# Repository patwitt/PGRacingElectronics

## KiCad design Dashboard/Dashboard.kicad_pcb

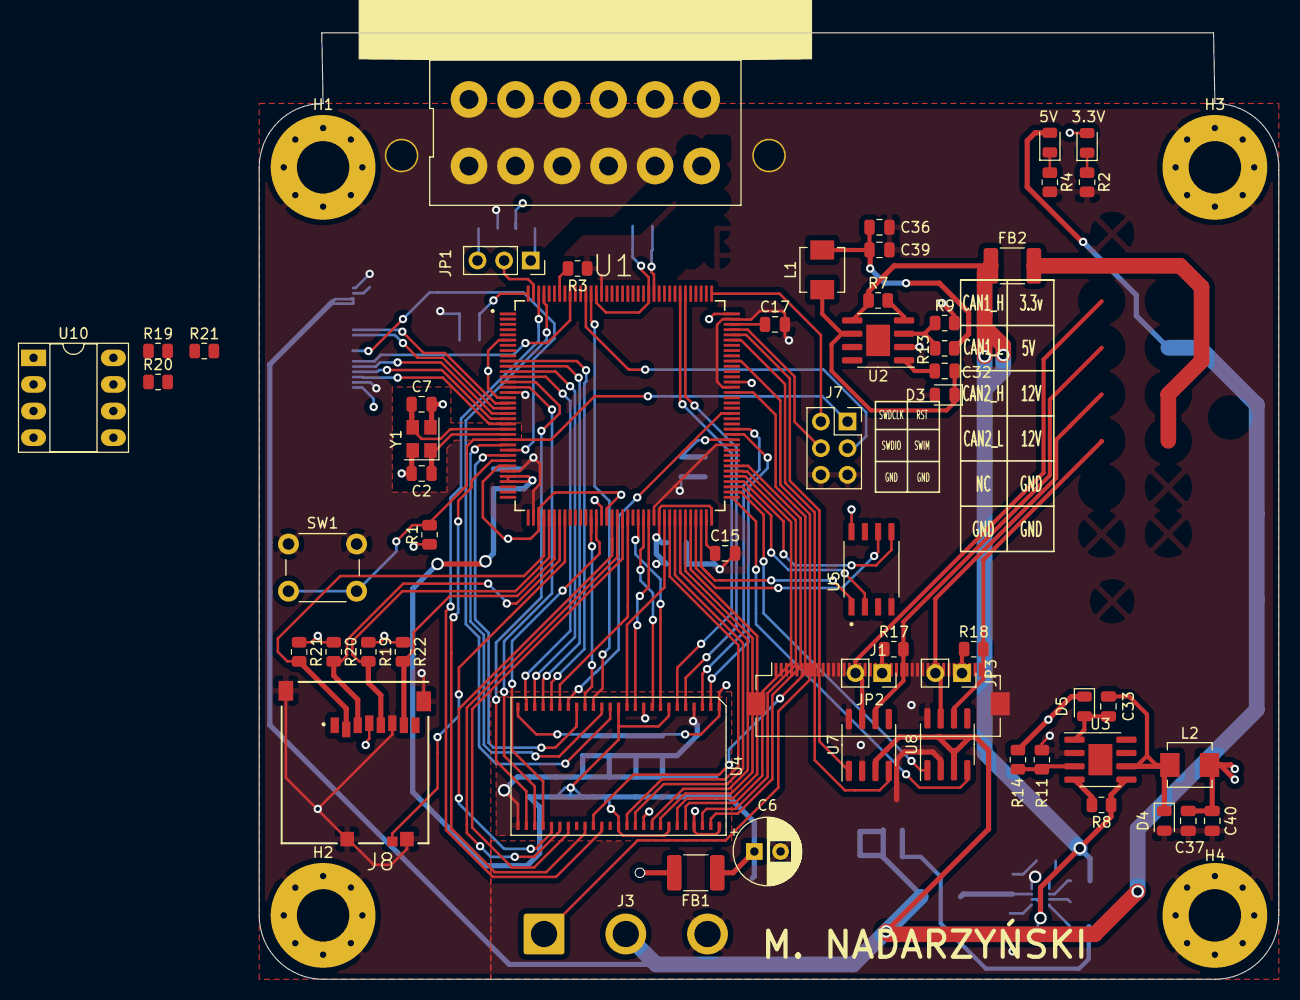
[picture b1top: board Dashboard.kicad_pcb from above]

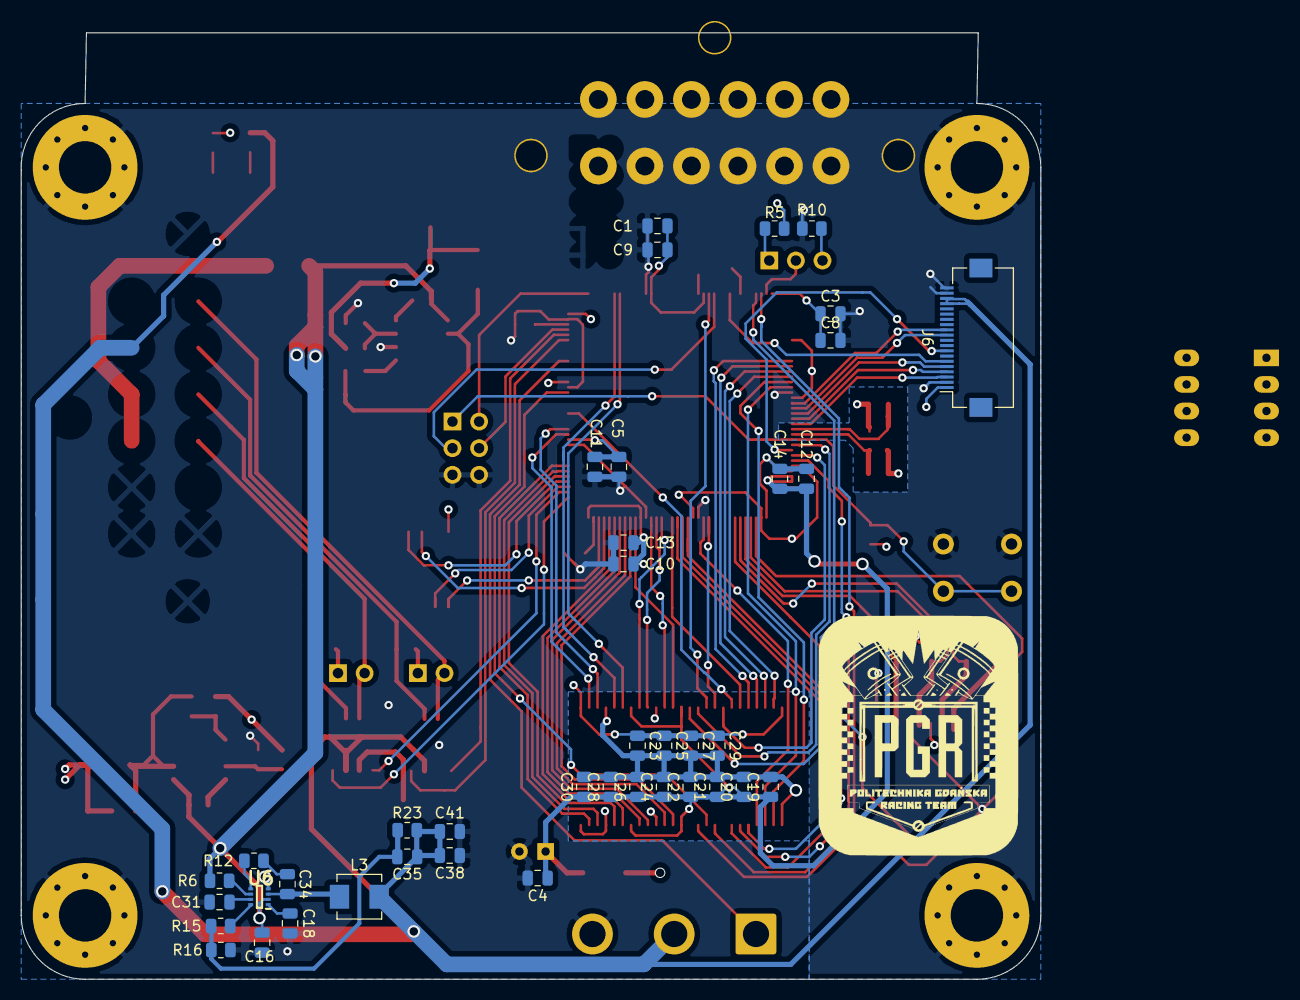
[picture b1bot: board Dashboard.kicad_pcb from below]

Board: 4 copper layers, 97.3 x 90.3 mm, 101 parts (40 on the bottom side), 125 nets.

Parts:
C1, C3, C4, C5, C8, C9, C10, C11, C13, C16, C19, C20, C21, C22, C23, C24, C25, C26, C27, C28, C29, C30: 100nF; C_0805_2012Metric
C2, C7: 14p; C_0805_2012Metric
C6: 470uF; CP_Radial_D6.3mm_P2.50mm
C12, C18, C31, C34: 1uF; C_0805_2012Metric
C14, C32, C33: 10nF; C_0805_2012Metric
C15, C17: 2.2uF; C_0805_2012Metric
C35: 10pF; C_0805_2012Metric
C36, C37, C39, C40: 10uF; C_0805_2012Metric
C38, C41: 22uF; C_0805_2012Metric
D1: LED_3.3V; LED_0805_2012Metric
D2: LED_5V; LED_0805_2012Metric
D3, D4: D_Schottky; D_0805_2012Metric
D5: 1N4148; D_0805_2012Metric
FB1, FB2: Ferrite_Bead; C_1812_4532Metric
H1, H2, H3, H4: MountingHole_Pad; MountingHole_5mm_Pad_Via
J1: Display; Hirose_FH12-40S-0.5SH_1x40-1MP_P0.50mm_Horizontal
J3: LED; SolderWire-2sqmm_1x03_P7.8mm_D2mm_OD3.9mm
J4: MAIN_CONNECTOR; DT13
J6: Display; Hirose_FH12-20S-0.5SH_1x20-1MP_P0.50mm_Horizontal
J7: PROGRAMMER; PinSocket_2x03_P2.54mm_Vertical
J8: MEM2051-00-195-00-A_REVC; GCT_MEM2051-00-195-00-A_REVC
JP1: PDR_ON; PinSocket_1x03_P2.54mm_Vertical
JP2: CAN1_RESISTOR; PinSocket_1x02_P2.54mm_Vertical
JP3: CAN2_RESISTOR; PinSocket_1x02_P2.54mm_Vertical
L1, L2: 10uH; L_Vishay_IHLP-1616
L3: 2.2uH; L_Vishay_IHLP-1616
R1, R3, R5, R10, R19, R20, R21: 10k; R_0805_2012Metric
R2, R4, R9, R11, R12, R13, R14: R; R_0805_2012Metric
R6, R7, R8: 100k; R_0805_2012Metric
R15: 20k; R_0805_2012Metric
R16: 13k; R_0805_2012Metric
R17, R18: 120; R_0805_2012Metric
R19#2, R20#2, R21#2, R22: 47K; R_0805_2012Metric
R23: 40.2k; R_0805_2012Metric
SW1: SW_SPST; SW_PUSH_6mm_H8mm
U1: STM32F767ZIT6; QFP50P2200X2200X160-144N
U2, U3: MP2359DJ-LF-Z; SOIC-8-1EP_3.9x4.9mm_P1.27mm_EP2.29x3mm
U4: AS4C1M16S-6TCN; TSOP-II-50
U5: AT25SF128A-SHB-T; SOIC127P790X216-8N
U6: MP2332H; SOTFL50P160X60-8N
U7, U8: MCP2561-E-SN; SOIC-8_3.9x4.9mm_P1.27mm
U10: 24LC01; DIP-8_W7.62mm_Socket_LongPads
Y1: Crystal_GND24; Crystal_SMD_3225-4Pin_3.2x2.5mm

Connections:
+3.3VA: C4.1, C6.1, C12.1, C14.1, C19.1, C20.1, C21.1, C22.1, C24.1, C26.1, C28.1, C30.1, FB1.1, U1.32, U1.33, U4.7, U4.13, U4.38, U4.44
+3V3: C1.1, C3.1, C5.1, C8.1, C9.1, C10.1, C11.1, C13.1, C23.1, C25.1, C27.1, C29.1, C37.2, C40.2, D1.2, D5.1, FB1.2, J1.4, J4.12, J6.1, J8.4, L2.2, R1.1, R5.1, R14.2, R19#2.1, R20#2.1, R21#2.1, R22.1, U1.6, U1.17, U1.30, U1.39, U1.52, U1.62, U1.72, U1.84, U1.95, U1.108, U1.121, U1.131, U1.144, U4.1, U4.25, U5.8, U10.8
+5V: C35.2, C38.2, C41.2, D2.2, J1.2, J3.2, J4.11, J6.17, J6.18, L3.2, R23.2, U7.3, U8.3
+8V: C36.2, C39.2, L1.2, R13.2
+12L: C16.1, FB2.1, R6.1, R7.1, R8.1, U2.5, U3.5, U6.2
+12V: FB2.2, J4.9, J4.10
/FMC_A0: U1.10, U4.21
/FMC_A1: U1.11, U4.22
/FMC_A2: U1.12, U4.23
/FMC_A3: U1.13, U4.24
/FMC_A4: U1.14, U4.27
/FMC_A5: U1.15, U4.28
/FMC_A6: U1.50, U4.29
/FMC_A7: U1.53, U4.30
/FMC_A8: U1.54, U4.31
/FMC_A9: U1.55, U4.32
/FMC_A10: U1.56, U4.20
/FMC_BA0: U1.89, U4.19
/FMC_D0: U1.85, U4.2
/FMC_D1: U1.86, U4.3
/FMC_D2: U1.114, U4.5
/FMC_D3: U1.115, U4.6
/FMC_D4: U1.58, U4.8
/FMC_D5: U1.59, U4.9
/FMC_D6: U1.60, U4.11
/FMC_D7: U1.63, U4.12
/FMC_D8: U1.64, U4.39
/FMC_D9: U1.65, U4.40
/FMC_D10: U1.66, U4.42
/FMC_D11: U1.67, U4.43
/FMC_D12: U1.68, U4.45
/FMC_D13: U1.77, U4.46
/FMC_D14: U1.78, U4.48
/FMC_D15: U1.79, U4.49
/FMC_NBL0: U1.141, U4.14
/FMC_NBL1: U1.142, U4.36
/FMC_SDCAS: U1.132, U4.16
/FMC_SDCKE0: U1.29, U4.34
/FMC_SDCLK: U1.93, U4.35
/FMC_SDNE0: U1.28, U4.18
/FMC_SDNRAS: U1.49, U4.17
/FMC_SDNWE: U1.43, U4.15
/I2C3_SCL: U1.100, U10.6
/I2C3_SDA: U1.99, U10.5
/LTDC_B0: J1.21, U1.3
/LTDC_B1: J1.22, U1.102
/LTDC_B2: J1.23, U1.122
/LTDC_B3: J1.24, U1.126
/LTDC_B4: J1.25, U1.127
/LTDC_B5: J1.26, U1.37
/LTDC_B6: J1.27, U1.139
/LTDC_B7: J1.28, U1.140
/LTDC_CLK: J1.30, U1.92
/LTDC_DE: J1.34, U1.22
/LTDC_G0: J1.13, U1.4
/LTDC_G1: J1.14, U1.5
/LTDC_G2: J1.15, U1.42
/LTDC_G3: J1.16, U1.125
/LTDC_G4: J1.17, U1.69
/LTDC_G5: J1.18, U1.70
/LTDC_G6: J1.19, U1.97
/LTDC_G7: J1.20, U1.117
/LTDC_HSYNC: J1.32, U1.96
/LTDC_R0: J1.5, U1.128
/LTDC_R1: J1.6, U1.36
/LTDC_R2: J1.7, U1.35
/LTDC_R3: J1.8, U1.46
/LTDC_R4: J1.9, U1.41
/LTDC_R5: J1.10, U1.26
/LTDC_R6: J1.11, U1.47
/LTDC_R7: J1.12, U1.91
/LTDC_VSYNC: J1.33, U1.40
/QUADSPI_IO0: U1.20, U5.5
/QUADSPI_IO1: U1.21, U5.2
/QUADSPI_IO2: U1.19, U5.3
/QUADSPI_IO3: U1.18, U5.7
/QUADSPI_NCS: U1.136, U5.1
/SD_CARD_DETECT: J8.9, U1.44
/SD_CS: J8.2, R21#2.2
/SD_MISO: J8.7, R22.2
/SD_MOSI: J8.3, R20#2.2
/SD_SCLK: J8.5, R19#2.2
CAN_1_1: U1.104, U7.1
CAN_1_2: U1.103, U7.4
CAN_2_1: U1.74, U8.1
CAN_2_2: U1.73, U8.4
CAN_H1: J4.1, JP2.2, U7.7
CAN_H2: J4.3, JP3.2, U8.7
CAN_L1: J4.2, R17.2, U7.6
CAN_L2: J4.4, R18.2, U8.6
GND: C1.2, C2.2, C3.2, C4.2, C5.2, C6.2, C7.2, C8.2, C9.2, C10.2, C11.2, C12.2, C13.2, C14.2, C15.2, C16.2, C17.2, C18.1, C19.2, C20.2, C21.2, C22.2, C23.2, C24.2, C25.2, C26.2, C27.2, C28.2, C29.2, C30.2, C31.1, C36.1, C37.1, C38.1, C39.1, C40.1, C41.1, D3.2, D4.2, H1.1, H2.1, H3.1, H4.1, J1.1, J1.3, J1.29, J1.36, J3.3, J4.6, J4.7, J4.8, J4.14, J4.15, J6.2, J6.19, J6.20, J7.5, J7.6, J8.6, J8.10, J8.11, J8.12, J8.13, R2.2, R3.1, R4.2, R9.2, R10.2, R11.2, R16.2, R21.1, SW1.1, U1.16, U1.31, U1.38, U1.51, U1.61, U1.83, U1.94, U1.107, U1.120, U1.130, U2.2, U3.2, U4.4, U4.10, U4.26, U4.41, U4.47, U4.50, U5.4, U6.4, U7.2, U7.8, U8.2, U8.8, U10.1, U10.2, U10.3, U10.4, Y1.2, Y1.4
LED_DATA: J3.1, U1.134
unnamed: C2.1, U1.24, Y1.1
unnamed: C7.1, U1.23, Y1.3
unnamed: C18.2, U6.1
unnamed: C31.2, U6.7
unnamed: C32.1, U2.1
unnamed: C32.2, D3.1, L1.1, U2.6
unnamed: C33.1, D5.2, U3.1
unnamed: C33.2, D4.1, L2.1, U3.6
unnamed: C34.1, R12.1
unnamed: C34.2, L3.1, U6.3
unnamed: C35.1, R15.1, R16.1, R23.1
unnamed: D1.1, R2.1
unnamed: D2.1, R4.1
unnamed: JP1.1, R5.2
unnamed: JP1.2, U1.143
unnamed: JP1.3, R10.1
unnamed: JP2.1, R17.1
unnamed: JP3.1, R18.1
unnamed: R3.2, U1.138
unnamed: R6.2, U6.6
unnamed: R7.2, U2.4
unnamed: R8.2, U3.4
unnamed: R11.1, R14.1, U3.3
unnamed: R12.2, U6.5
unnamed: R9.1, R13.1, U2.3
unnamed: R15.2, U6.8
unnamed: R21.2, U10.7
RST: J7.1, R1.2, SW1.2, U1.25
SWDCLK: J7.2, U1.109
SWDIO: J7.4, U1.105
SWIM: J7.3, U1.133
VCAP1: C15.1, U1.71
VCAP2: C17.1, U1.106

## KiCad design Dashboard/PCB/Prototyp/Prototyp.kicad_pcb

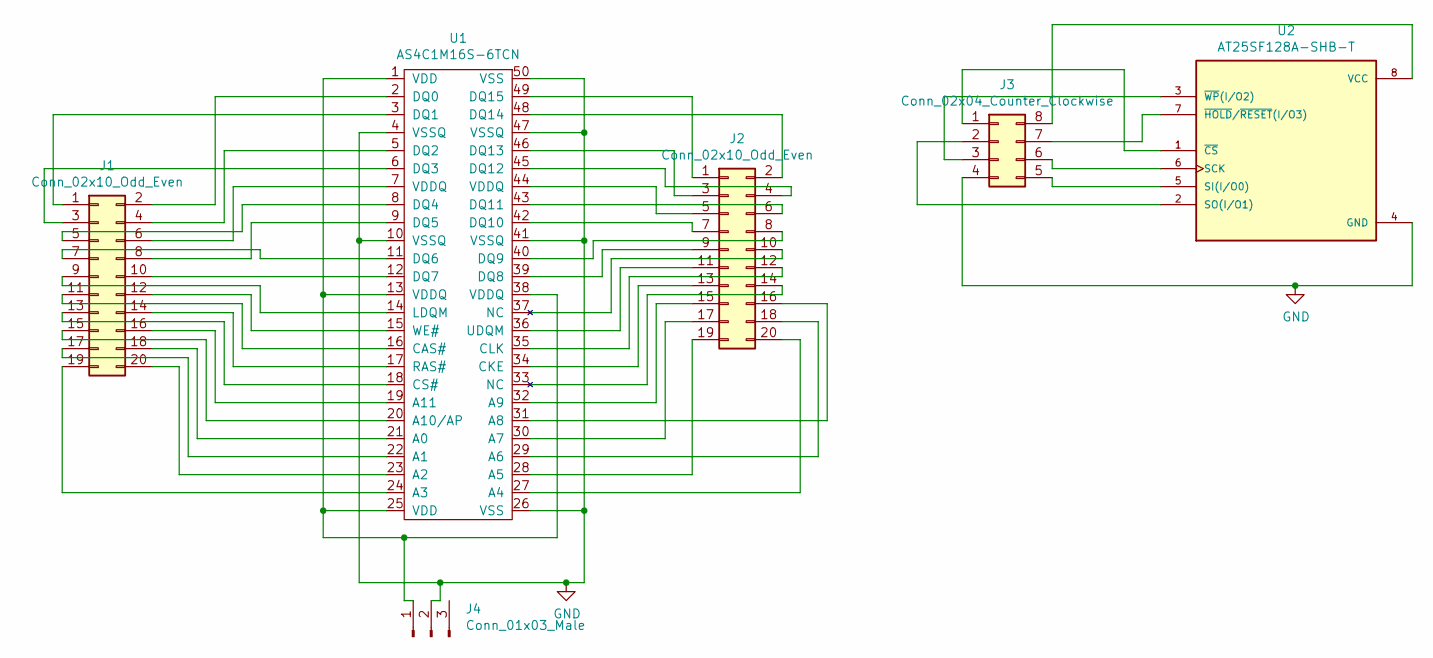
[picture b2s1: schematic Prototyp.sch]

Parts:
J1, J2: Conn_02x10_Odd_Even; PinSocket_2x10_P2.54mm_Vertical
J3: Conn_02x04_Counter_Clockwise; PinSocket_2x04_P2.54mm_Vertical
J4: Conn_01x03_Male; PinSocket_1x03_P2.54mm_Vertical
U1: AS4C1M16S-6TCN; TSOP-II-50
U2: AT25SF128A-SHB-T; SOIC127P790X216-8N; PARTREV F

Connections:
GND: J3.4, J4.2, U1.4 (VSSQ), U1.10 (VSSQ), U1.26 (VSS), U1.41 (VSSQ), U1.47 (VSSQ), U1.50 (VSS), U2.4 (GND)
unnamed: J1.1, U1.3 (DQ1)
unnamed: J1.2, U1.2 (DQ0)
unnamed: J1.3, U1.6 (DQ3)
unnamed: J1.4, U1.5 (DQ2)
unnamed: J1.5, U1.8 (DQ4)
unnamed: J1.6, U1.7 (VDDQ)
unnamed: J1.7, U1.11 (DQ6)
unnamed: J1.8, U1.9 (DQ5)
unnamed: J1.9, U1.14 (LDQM)
unnamed: J1.10, U1.12 (DQ7)
unnamed: J1.11, U1.16 (CAS#)
unnamed: J1.12, U1.15 (WE#)
unnamed: J1.13, U1.18 (CS#)
unnamed: J1.14, U1.17 (RAS#)
unnamed: J1.15, U1.20 (A10/AP)
unnamed: J1.16, U1.19 (A11)
unnamed: J1.17, U1.22 (A1)
unnamed: J1.18, U1.21 (A0)
unnamed: J1.19, U1.24 (A3)
unnamed: J1.20, U1.23 (A2)
unnamed: J2.1, U1.49 (DQ15)
unnamed: J2.2, U1.48 (DQ14)
unnamed: J2.3, U1.46 (DQ13)
unnamed: J2.4, U1.45 (DQ12)
unnamed: J2.5, U1.44 (VDDQ)
unnamed: J2.6, U1.43 (DQ11)
unnamed: J2.7, U1.42 (DQ10)
unnamed: J2.8, U1.40 (DQ9)
unnamed: J2.9, U1.39 (DQ8)
unnamed: J2.10, U1.37 (NC)
unnamed: J2.11, U1.36 (UDQM)
unnamed: J2.12, U1.35 (CLK)
unnamed: J2.13, U1.34 (CKE)
unnamed: J2.14, U1.33 (NC)
unnamed: J2.15, U1.32 (A9)
unnamed: J2.16, U1.31 (A8)
unnamed: J2.17, U1.30 (A7)
unnamed: J2.18, U1.29 (A6)
unnamed: J2.19, U1.28 (A5)
unnamed: J2.20, U1.27 (A4)
unnamed: J3.1, U2.1 (~CS)
unnamed: J3.2, U2.2 (SO(I/O1))
unnamed: J3.3, U2.3 (~WP~(I/O2))
unnamed: J3.5, U2.5 (SI(I/O0))
unnamed: J3.6, U2.6 (SCK)
unnamed: J3.7, U2.7 (~HOLD~/~RESET~(I/O3))
unnamed: J3.8, U2.8 (VCC)
unnamed: J4.1, U1.1 (VDD), U1.13 (VDDQ), U1.25 (VDD), U1.38 (VDDQ)

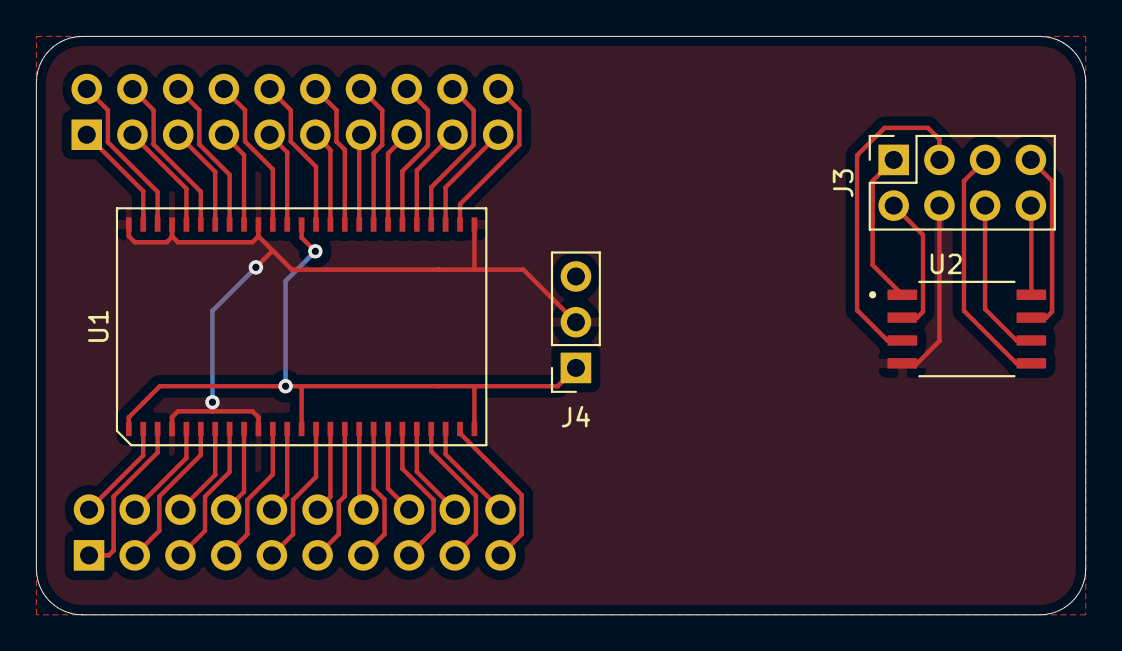
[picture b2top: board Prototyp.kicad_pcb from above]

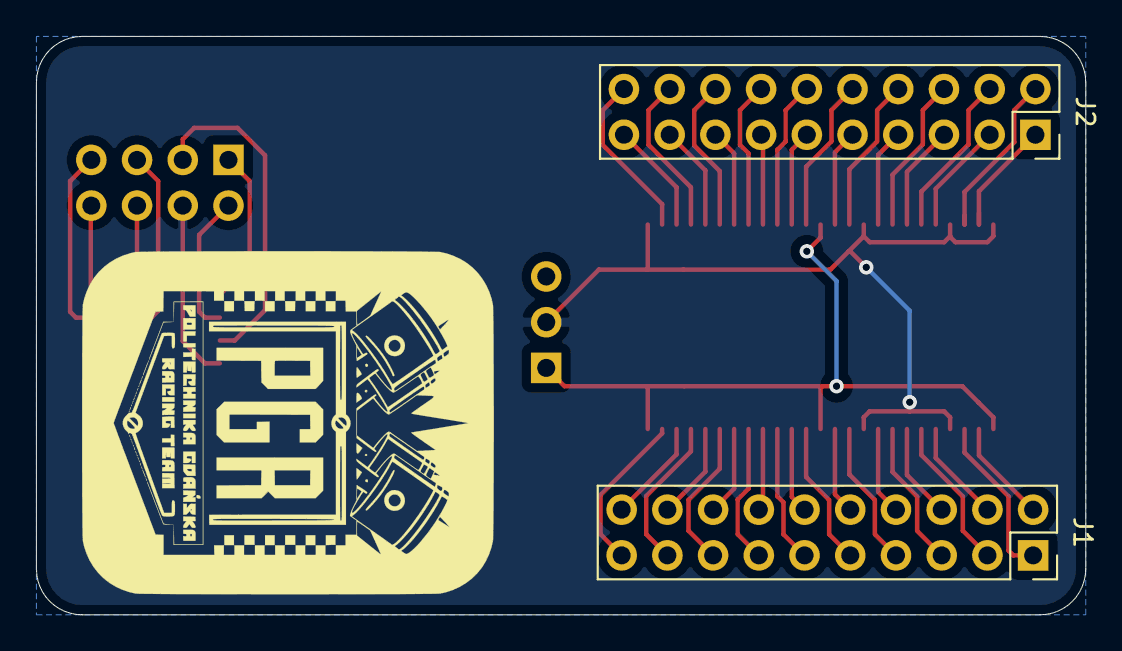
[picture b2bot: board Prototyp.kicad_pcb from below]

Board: 2 copper layers, 58.3 x 32.1 mm, 6 parts (2 on the bottom side), 49 nets.

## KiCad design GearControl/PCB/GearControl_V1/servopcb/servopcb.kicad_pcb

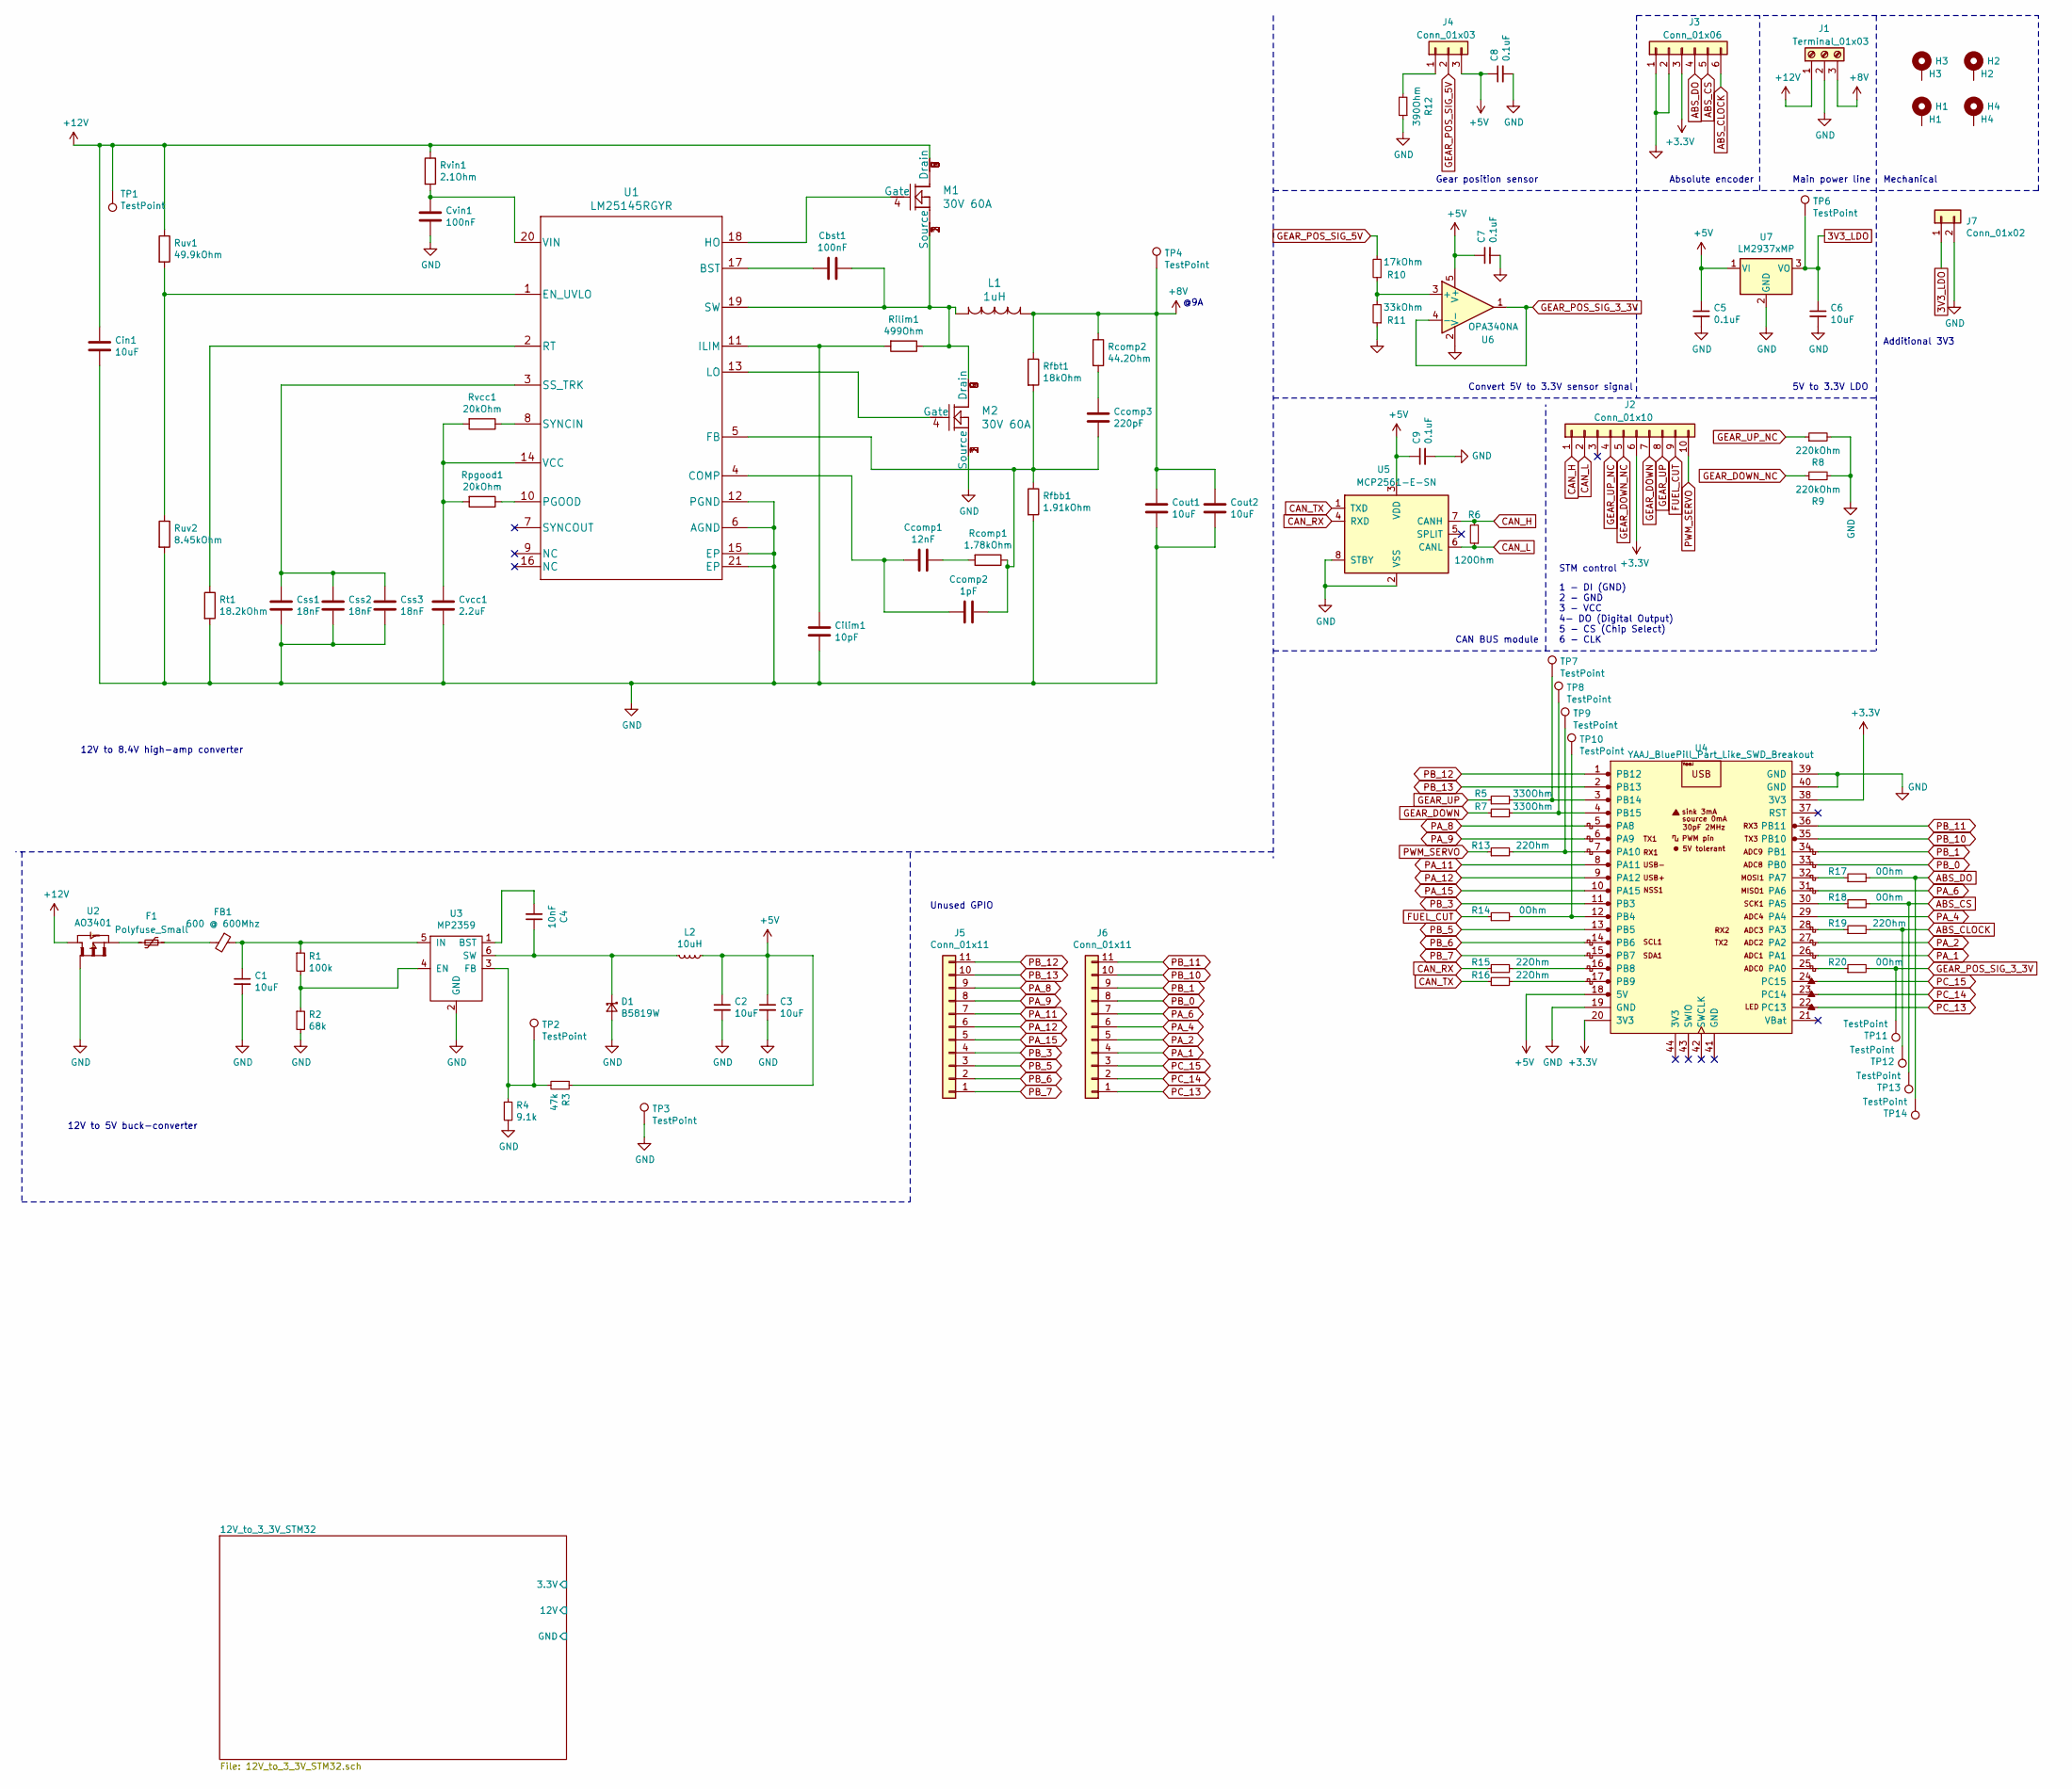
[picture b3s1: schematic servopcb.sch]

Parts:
C1, C2, C3: 10uF; C_1206_3216Metric
C4: 10nF; C_0603_1608Metric
C5, C7: 0.1uF; C_0805_2012Metric
C6: 10uF; C_0805_2012Metric
C8, C9: 0.1uF; C_0603_1608Metric
Cbst1: 100nF; C_0603_1608Metric
Ccomp1: 12nF; C_0402_1005Metric
Ccomp2: 1pF; C_0402_1005Metric
Ccomp3: 220pF; C_0402_1005Metric
Cilim1: 10pF; C_0603_1608Metric
Cin1: 10uF; C_1210_3225Metric
Cout1, Cout2: 10uF; C_1210_3225Metric
Css1, Css2, Css3: 18nF; C_0402_1005Metric
Cvcc1: 2.2uF; C_0402_1005Metric
Cvin1: 100nF; C_0603_1608Metric
D1: B5819W; D_SOD-123
F1: Polyfuse_Small; Fuse_1206_3216Metric
FB1: 600 @ 600Mhz; L_0805_2012Metric
H1: H1; MountingHole_4mm_Pad_Via
H2: H2; MountingHole_4mm_Pad_Via
H3: H3; MountingHole_4mm_Pad_Via
H4: H4; MountingHole_4mm_Pad_Via
J1: Terminal_01x03; TerminalBlock_Phoenix_PT-1,5-3-5.0-H_1x03_P5.00mm_Horizontal
J2: Conn_01x10; Molex_PicoBlade_53398-1071_1x10-1MP_P1.25mm_Vertical
J3: Conn_01x06; Molex_PicoBlade_53398-0671_1x06-1MP_P1.25mm_Vertical
J4: Conn_01x03; Molex_PicoBlade_53398-0371_1x03-1MP_P1.25mm_Vertical
J5, J6: Conn_01x11; PinHeader_1x11_P2.54mm_Vertical
J7: Conn_01x02; PinHeader_1x02_P2.54mm_Vertical
L1: 1uH; IHLP3232DZER1R0M01
L2: 10uH; L_7.3x7.3_H4.5
M1: 30V 60A; CSD17309Q3
M2: 30V 60A; CSD17575Q3
R1: 100k; R_0603_1608Metric
R2: 68k; R_0603_1608Metric
R3: 47k; R_0603_1608Metric
R4: 9.1k; R_0603_1608Metric
R5, R7: 330Ohm; R_0603_1608Metric
R6: 120Ohm; R_0603_1608Metric
R8, R9: 220kOhm; R_0603_1608Metric
R10: 17kOhm; R_0603_1608Metric
R11: 33kOhm; R_0603_1608Metric
R12: 390Ohm; R_0603_1608Metric
R13, R15, R16, R19: 22Ohm; R_0603_1608Metric
R14, R17, R18, R20: 0Ohm; R_0603_1608Metric
Rcomp1: 1.78kOhm; R_0402_1005Metric
Rcomp2: 44.2Ohm; R_0402_1005Metric
Rfbb1: 1.91kOhm; R_0402_1005Metric
Rfbt1: 18kOhm; R_0603_1608Metric
Rilim1: 499Ohm; R_0402_1005Metric
Rpgood1: 20kOhm; R_0402_1005Metric
Rt1: 18.2kOhm; R_0402_1005Metric
Ruv1: 49.9kOhm; R_0402_1005Metric
Ruv2: 8.45kOhm; R_0603_1608Metric
Rvcc1: 20kOhm; R_0402_1005Metric
Rvin1: 2.1Ohm; R_0603_1608Metric
TP1, TP2, TP3, TP4, TP6, TP7, TP8, TP9, TP10, TP11, TP12, TP13, TP14: TestPoint; TestPoint_Pad_D1.0mm
U1: LM25145RGYR
U2: AO3401; SOT23
U3: MP2359; MP2359DJ-LF-Z
U4: YAAJ_BluePill_Part_Like_SWD_Breakout; YAAJ_BluePill_2
U5: MCP2561-E-SN; SOIC-8_3.9x4.9mm_P1.27mm
U6: OPA340NA; SOT-23-5
U7: LM2937xMP; SOT-223-3_TabPin2

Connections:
3V3_LDO: C6.1, J7.1, TP6.1, U7.3 (VO)
+3V3: J2.6, J3.3, U4.20 (3V3), U4.38 (3V3)
+5V: C2.1, C3.1, C5.1, C7.1, C8.1, C9.1, J4.3, L2.1, R3.1, U4.18 (5V), U5.3 (VDD), U6.5 (V+), U7.1 (VI)
+8V: Cout1.1, Cout2.1, J1.3, L1.1, Rcomp2.1, Rfbt1.1, TP4.1
+12V: Cin1.1, J1.1, M1.5 (Drain), M1.6 (Drain), M1.7 (Drain), M1.8 (Drain), M1.9 (Drain), M1.V, Ruv1.1, Rvin1.1, TP1.1, U2.3
ABS_CLOCK: J3.6, R19.2, TP12.1
ABS_CS: J3.5, R18.2, TP13.1
ABS_DO: J3.4, R17.2, TP14.1
CAN_H: J2.1, R6.2, U5.7 (CANH)
CAN_L: J2.2, R6.1, U5.6 (CANL)
CAN_RX: R15.1, U5.4 (RXD)
CAN_TX: R16.1, U5.1 (TXD)
FUEL_CUT: J2.9, R14.1
GEAR_DOWN: J2.7, R7.1
GEAR_DOWN_NC: J2.5, R9.1
GEAR_POS_SIG_3_3V: R20.2, TP11.1, U6.1, U6.4 (-)
GEAR_POS_SIG_5V: J4.2, R10.2
GEAR_UP: J2.8, R5.1
GEAR_UP_NC: J2.4, R8.1
GND: C1.2, C2.2, C3.2, C5.2, C6.2, C7.2, C8.2, C9.2, Cilim1.2, Cin1.2, Cout1.2, Cout2.2, Css1.2, Css2.2, Css3.2, Cvcc1.2, Cvin1.2, D1.2 (A), J1.2, J3.1, J3.2, J7.2, M2.1 (Source), M2.2 (Source), M2.3 (Source), R2.2, R4.2, R8.2, R9.2, R11.1, R12.1, Rfbb1.2, Rt1.2, Ruv2.2, TP3.1, U1.6 (AGND), U1.12 (PGND), U1.15 (EP), U1.21 (EP), U1.V, U2.1, U3.2 (GND), U4.19 (GND), U4.39 (GND), U4.40 (GND), U5.2 (VSS), U5.8 (STBY), U6.2 (V-), U7.2 (GND)
unnamed: C1.1, FB1.1, R1.1, U3.5 (IN)
unnamed: C4.1, D1.1 (K), L2.2, U3.6 (SW)
unnamed: C4.2, U3.1 (BST)
unnamed: Cbst1.1, L1.2, M1.1 (Source), M1.2 (Source), M1.3 (Source), M2.5 (Drain), M2.6 (Drain), M2.7 (Drain), M2.8 (Drain), M2.9 (Drain), M2.V, Rilim1.1, U1.19 (SW)
unnamed: Cbst1.2, U1.17 (BST)
unnamed: Ccomp1.1, Rcomp1.2
unnamed: Ccomp1.2, Ccomp2.2, U1.4 (COMP)
unnamed: Ccomp2.1, Ccomp3.2, Rcomp1.1, Rfbb1.1, Rfbt1.2, U1.5 (FB)
unnamed: Ccomp3.1, Rcomp2.2
unnamed: Cilim1.1, Rilim1.2, U1.11 (ILIM)
unnamed: Css1.1, Css2.1, Css3.1, U1.3 (SS_TRK)
unnamed: Cvcc1.1, Rpgood1.2, Rvcc1.2, U1.14 (VCC)
unnamed: Cvin1.1, Rvin1.2, U1.20 (VIN)
unnamed: F1.1, FB1.2
unnamed: F1.2, U2.2
unnamed: J4.1, R12.2
unnamed: M1.4 (Gate), U1.18 (HO)
unnamed: M2.4 (Gate), U1.13 (LO)
unnamed: R1.2, R2.1, U3.4 (EN)
unnamed: R3.2, R4.1, TP2.1, U3.3 (FB)
unnamed: R5.2, TP7.1, U4.3 (PB14)
unnamed: R7.2, TP8.1, U4.4 (PB15)
unnamed: R10.1, R11.2, U6.3 (+)
unnamed: R13.2, TP9.1, U4.7 (PA10)
unnamed: R14.2, TP10.1, U4.12 (PB4)
unnamed: R15.2, U4.16 (PB8)
unnamed: R16.2, U4.17 (PB9)
unnamed: R17.1, U4.32 (PA7)
unnamed: R18.1, U4.30 (PA5)
unnamed: R19.1, U4.28 (PA3)
unnamed: R20.1, U4.25 (PA0)
unnamed: Rpgood1.1, U1.10 (PGOOD)
unnamed: Rt1.1, U1.2 (RT)
unnamed: Ruv1.2, Ruv2.1, U1.1 (EN_UVLO)
unnamed: Rvcc1.1, U1.8 (SYNCIN)
PA_1: J6.4, U4.26 (PA1)
PA_2: J6.5, U4.27 (PA2)
PA_4: J6.6, U4.29 (PA4)
PA_6: J6.7, U4.31 (PA6)
PA_8: J5.9, U4.5 (PA8)
PA_9: J5.8, U4.6 (PA9)
PA_11: J5.7, U4.8 (PA11)
PA_12: J5.6, U4.9 (PA12)
PA_15: J5.5, U4.10 (PA15)
PB_0: J6.8, U4.33 (PB0)
PB_1: J6.9, U4.34 (PB1)
PB_3: J5.4, U4.11 (PB3)
PB_5: J5.3, U4.13 (PB5)
PB_6: J5.2, U4.14 (PB6)
PB_7: J5.1, U4.15 (PB7)
PB_10: J6.10, U4.35 (PB10)
PB_11: J6.11, U4.36 (PB11)
PB_12: J5.11, U4.1 (PB12)
PB_13: J5.10, U4.2 (PB13)
PC_13: J6.1, U4.22 (PC13)
PC_14: J6.2, U4.23 (PC14)
PC_15: J6.3, U4.24 (PC15)
PWM_SERVO: J2.10, R13.1

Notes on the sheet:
12V to 5V buck-converter
12V to 8.4V high-amp converter
1 - DI (GND) 2 - GND 3 - VCC 4- DO (Digital Output) 5 - CS (Chip Select) 6 - CLK
5V to 3.3V LDO
Convert 5V to 3.3V sensor signal
Gear position sensor
Absolute encoder
Main power line
STM control
CAN BUS module
@9A
Unused GPIO
Mechanical
Additional 3V3

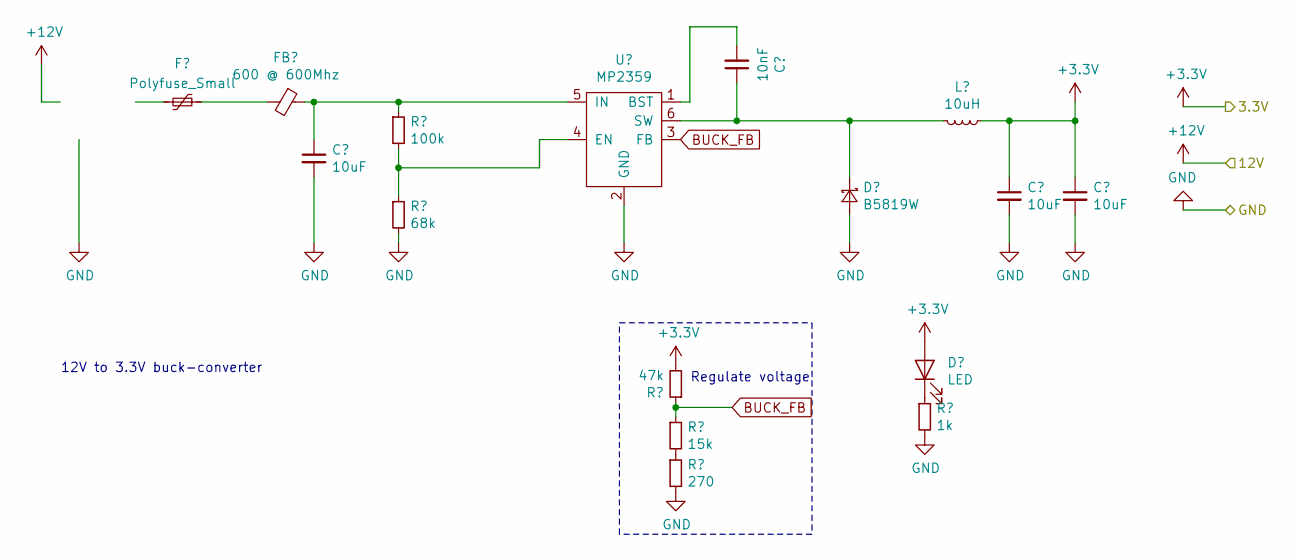
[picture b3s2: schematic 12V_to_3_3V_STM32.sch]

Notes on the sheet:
12V to 3.3V buck-converter
Regulate voltage

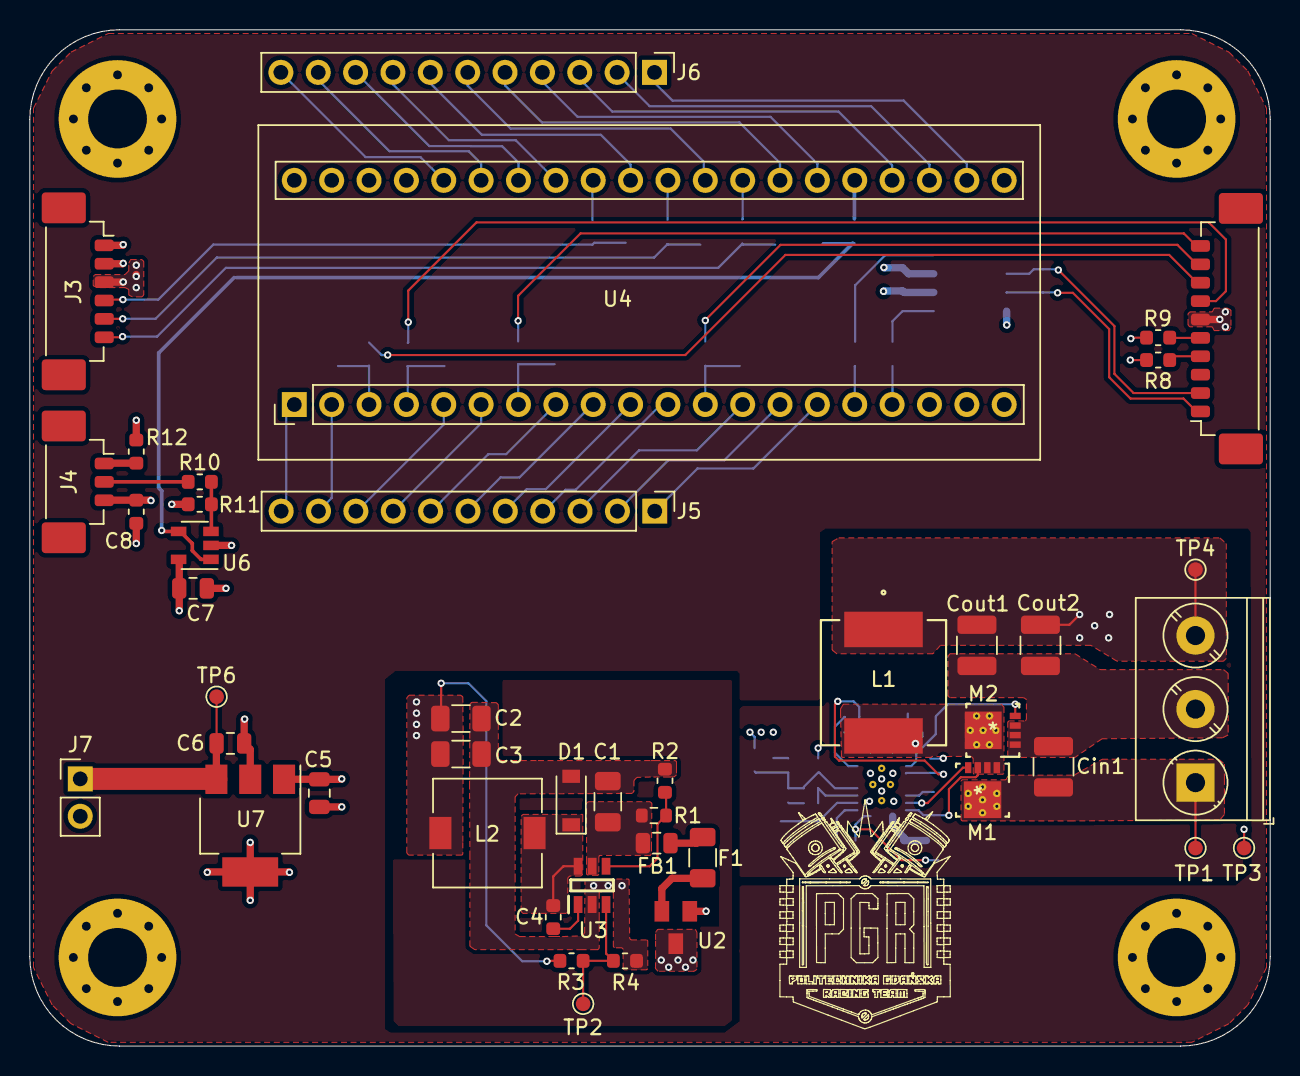
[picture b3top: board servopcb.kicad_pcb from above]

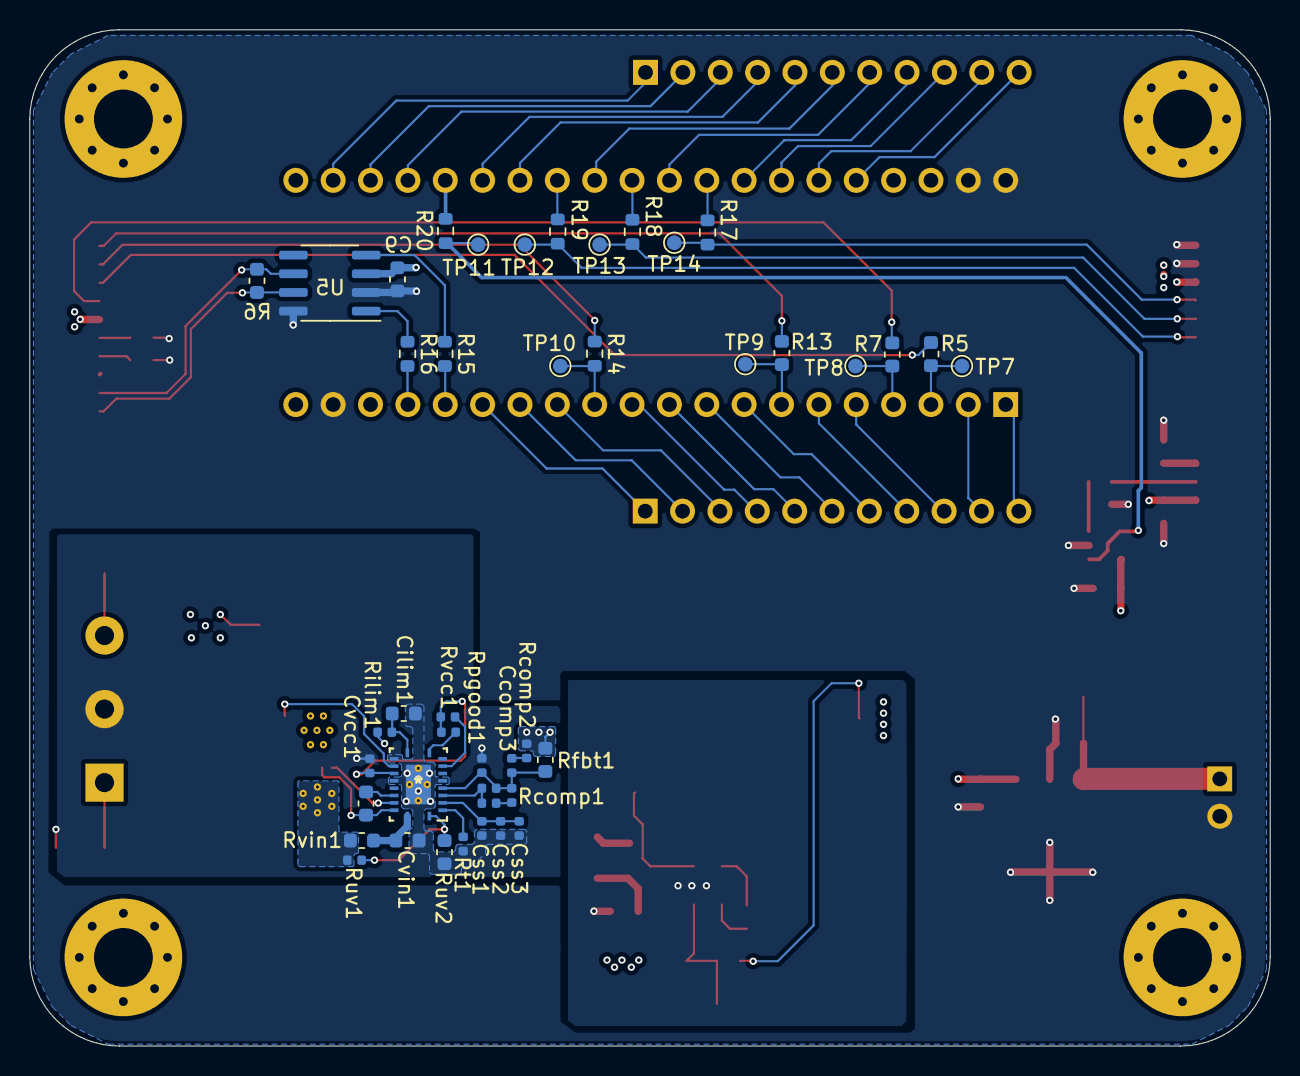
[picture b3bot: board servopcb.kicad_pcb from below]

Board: 4 copper layers, 84.3 x 69.1 mm, 91 parts (43 on the bottom side), 78 nets.

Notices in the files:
Dashboard/Code/Dashboard/Core/Src/can.c:
Copyright (c) 2022 STMicroelectronics.
All rights reserved.
This software is licensed under terms that can be found in the LICENSE file
Dashboard/Code/Dashboard/Core/Src/fmc.c:
Copyright (c) 2021 STMicroelectronics.
parts and their libraries:
Copyright 2016 Accelerated Designs. All rights reserved.
